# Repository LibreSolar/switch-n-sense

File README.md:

# Switch-N-Sense
High-side NMOS power switch and current sense resistor for battery applications

This device is the power part of the new generation Libre Solar 24V-48V BMS, but can also be used for lead-acid battery protection switches.

The connector to the BMS (IDC connector) is placed at the same height as in the BMS PCB. So mount this PCB right next to the BMS PCB (right side).

## Design considerations

The MOSFETs and the sense resistors are mounted at the back side of the PCB and should be attached to a large heat sink via thermal interface materials (e.g. thermal pad).

[Würth Power Elements WP-BUCF (order code 7461059)](https://powerelement.we-online.de/p/s/1406/93172-PowerOne-Bush-vertical-through-hole.html) are used for wire to board connection.

## Current target

Current rating can be adjusted depending on chosen MOSFETs and sense resistors.

- Maximum number of MOSFETs: 2 in parallel
- Maximum number of sense resitors (2512): 4

Targets for fully populated PCB (total heat dissipation approx. 20 W in MOSFETs, connectors and sense resistor at full current):

| MOSFET (2x) | Voltage | Maximum Current | Remark                                       |
|-------------|---------|-----------------|----------------------------------------------|
| FDMT80080DC | 48V     | 80 A            |                                              |
| FDMT80060DC | 12V/24V | 100 A           |                                              |
| CSD18540Q5B | 12V/24V | 60 A            | cheap alternative, but needs other footprint |

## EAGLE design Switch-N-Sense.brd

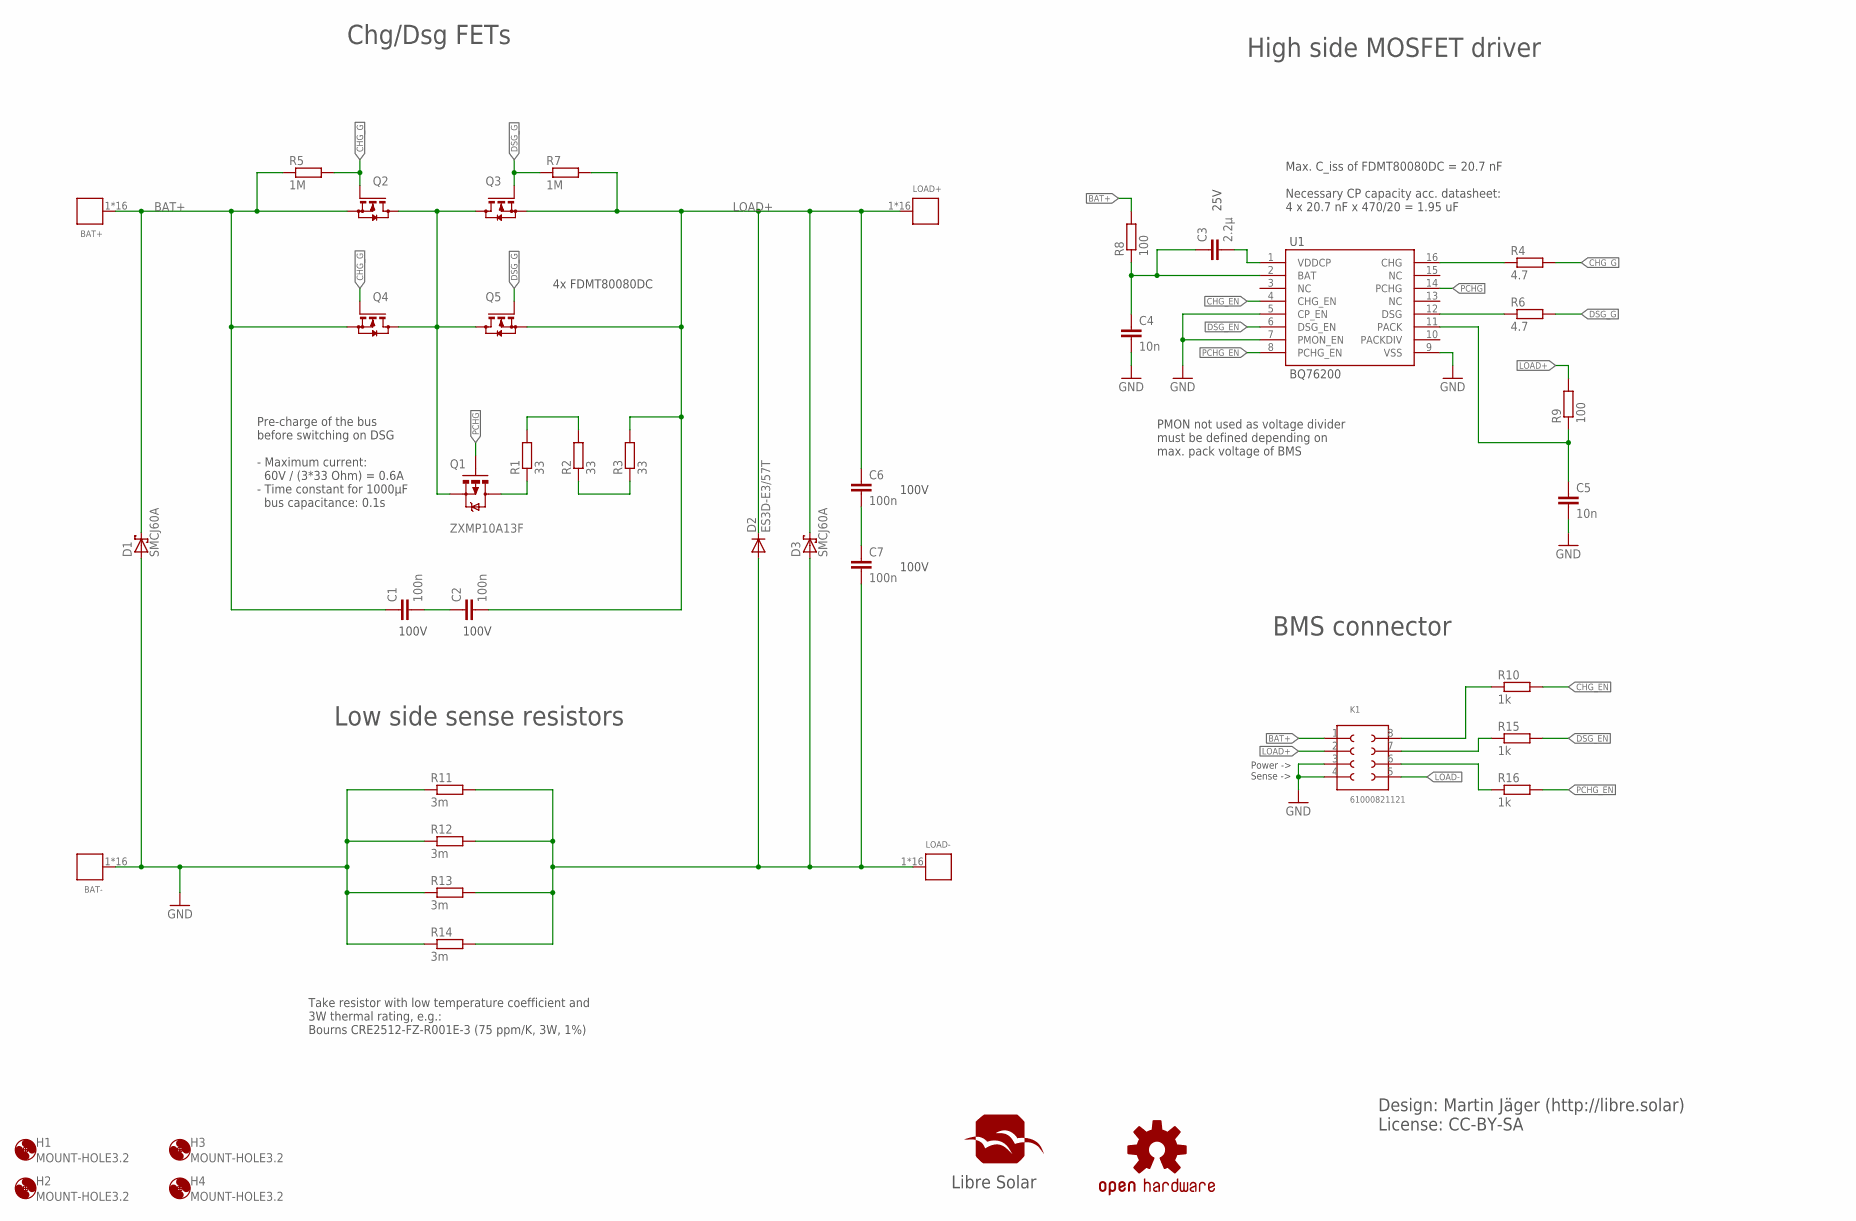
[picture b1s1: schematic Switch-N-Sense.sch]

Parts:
BAT+: WP-BUCF_G; 16PINS_CIR
BAT-: WP-BUCF_G; 16PINS_CIR
C1, C2, C6, C7: 100n; C0603; MPN 0603B104K500CT
C3: 2.2µ; C0805; MPN 0603B104K500CT
C4, C5: 10n; C0603; MPN GRM188R71H103KA01D.
D1, D3: SMCJ60A; SMC; MPN SMCJ75A
D2: ES3D-E3/57T; SMC; MPN ES3D-E3/57T.
H1, H2, H3, H4: MOUNT-HOLE3.2; 3,2
K1: 61000821121
LOAD+: WP-BUCF_G; 16PINS_CIR
LOAD-: WP-BUCF_G; 16PINS_CIR
N1: OSHW-LOGOM; OSHW-LOGO-M
Q1: ZXMP10A13F; SOT23-3; MPN ZXMP10A13FTA
Q2, Q3, Q4, Q5: FDMT80080DC
R1, R2, R3: 33; R2010; MPN ASC2010-33RFT4
R4, R6: 4.7; R0603; MPN ERJU06F1004V
R5, R7: 1M; R0603; MPN ERJU06F1004V
R8, R9: 100; R0603; MPN MCMR06X1001FTL
R10, R15, R16: 1k; R0603; MPN ERJU06F1004V
R11, R12, R13, R14: 3m; R2512
U1: BQ76200; TSSOP16
U$1: LIBRESOLAR_LOGO

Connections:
BAT+: BAT+.1, BAT+.2, BAT+.3, BAT+.4, BAT+.5, BAT+.6, BAT+.7, BAT+.8, BAT+.9, BAT+.10, BAT+.11, BAT+.12, BAT+.13, BAT+.14, BAT+.15, BAT+.16, C1.1, D1.C, K1.1, Q2.S, Q4.S, R5.1, R8.2
CHG: R4.1, U1.16 (CHG)
CHGDSG: Q1.2 (S), Q2.D, Q3.D, Q4.D, Q5.D
CHG_EN: R10.2, U1.4 (CHG_EN)
CHG_G: Q2.G, Q4.G, R4.2, R5.2
DSG: R6.1, U1.12 (DSG)
DSG_EN: R15.2, U1.6 (DSG_EN)
DSG_G: Q3.G, Q5.G, R6.2, R7.1
GND: BAT-.1, BAT-.2, BAT-.3, BAT-.4, BAT-.5, BAT-.6, BAT-.7, BAT-.8, BAT-.9, BAT-.10, BAT-.11, BAT-.12, BAT-.13, BAT-.14, BAT-.15, BAT-.16, C4.2, C5.2, D1.A, K1.3, K1.4, R11.1, R12.1, R13.1, R14.1, U1.5 (CP_EN), U1.7 (PMON_EN), U1.9 (VSS)
LOAD+: C2.2, C6.1, D2.C, D3.C, K1.2, LOAD+.1, LOAD+.2, LOAD+.3, LOAD+.4, LOAD+.5, LOAD+.6, LOAD+.7, LOAD+.8, LOAD+.9, LOAD+.10, LOAD+.11, LOAD+.12, LOAD+.13, LOAD+.14, LOAD+.15, LOAD+.16, Q3.S, Q5.S, R3.2, R7.2, R9.2
LOAD-: C7.2, D2.A, D3.A, K1.5, LOAD-.1, LOAD-.2, LOAD-.3, LOAD-.4, LOAD-.5, LOAD-.6, LOAD-.7, LOAD-.8, LOAD-.9, LOAD-.10, LOAD-.11, LOAD-.12, LOAD-.13, LOAD-.14, LOAD-.15, LOAD-.16, R11.2, R12.2, R13.2, R14.2
unnamed: C6.2, C7.1
unnamed: R1.2, R2.2
unnamed: R2.1, R3.1
unnamed: K1.7, R15.1
unnamed: K1.6, R16.1
unnamed: K1.8, R10.1
unnamed: C3.2, U1.1 (VDDCP)
unnamed: C3.1, C4.1, R8.1, U1.2 (BAT)
unnamed: C5.1, R9.1, U1.11 (PACK)
unnamed: C1.2, C2.1
unnamed: Q1.3 (D), R1.1
PCHG: Q1.1 (G), U1.14 (PCHG)
PCHG_EN: R16.2, U1.8 (PCHG_EN)

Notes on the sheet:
Pre-charge of the bus before switching on DSG - Maximum current: 60V / (3*33 Ohm) = 0.6A - Time constant for 1000µF bus capacitance: 0.1s
Chg/Dsg FETs
High side MOSFET driver
Design: Martin Jäger (http://libre.solar) License: CC-BY-SA
Max. C_iss of FDMT80080DC = 20.7 nF Necessary CP capacity acc. datasheet: 4 x 20.7 nF x 470/20 = 1.95 uF
4x FDMT80080DC
Take resistor with low temperature coefficient and 3W thermal rating, e.g.: Bourns CRE2512-FZ-R001E-3 (75 ppm/K, 3W, 1%)
Low side sense resistors
BMS connector
Power -> Sense ->
PMON not used as voltage divider must be defined depending on max. pack voltage of BMS
100V
25V

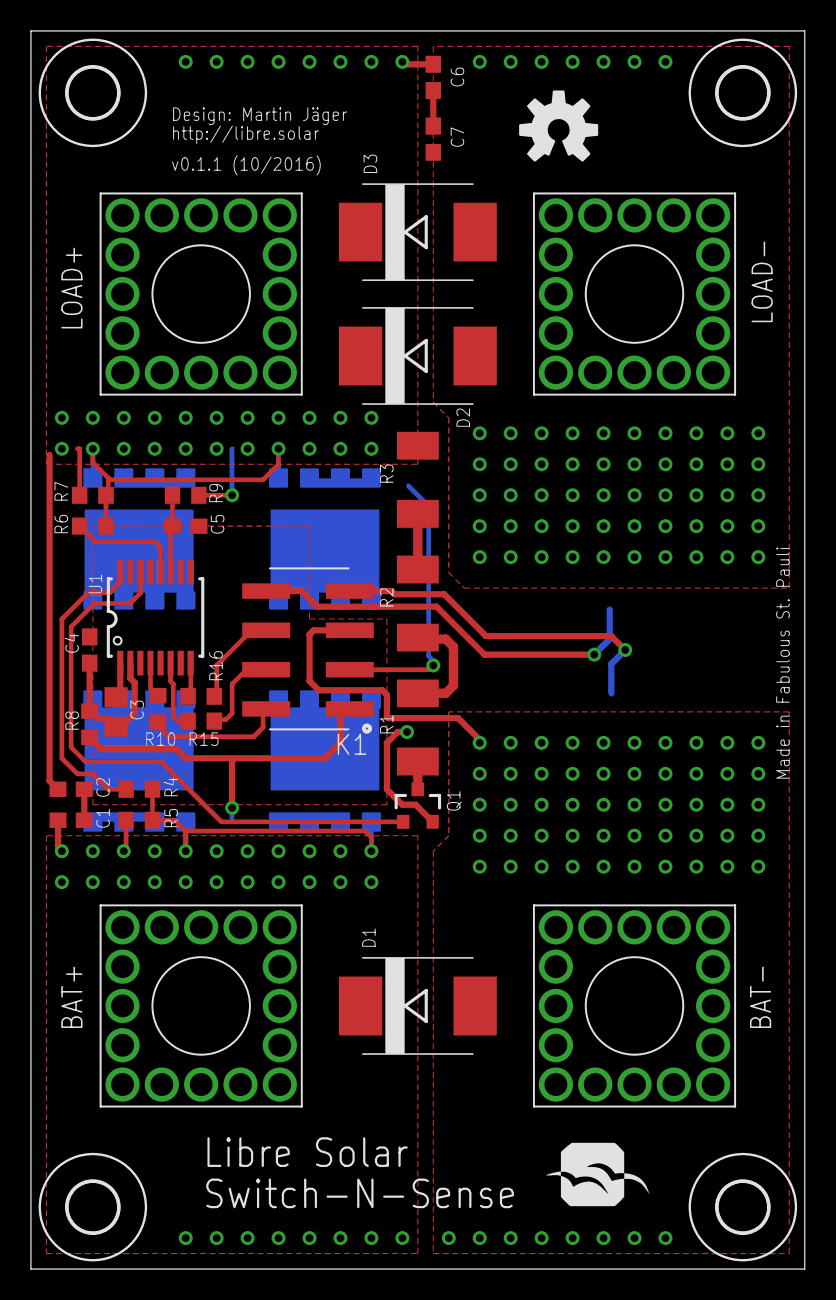
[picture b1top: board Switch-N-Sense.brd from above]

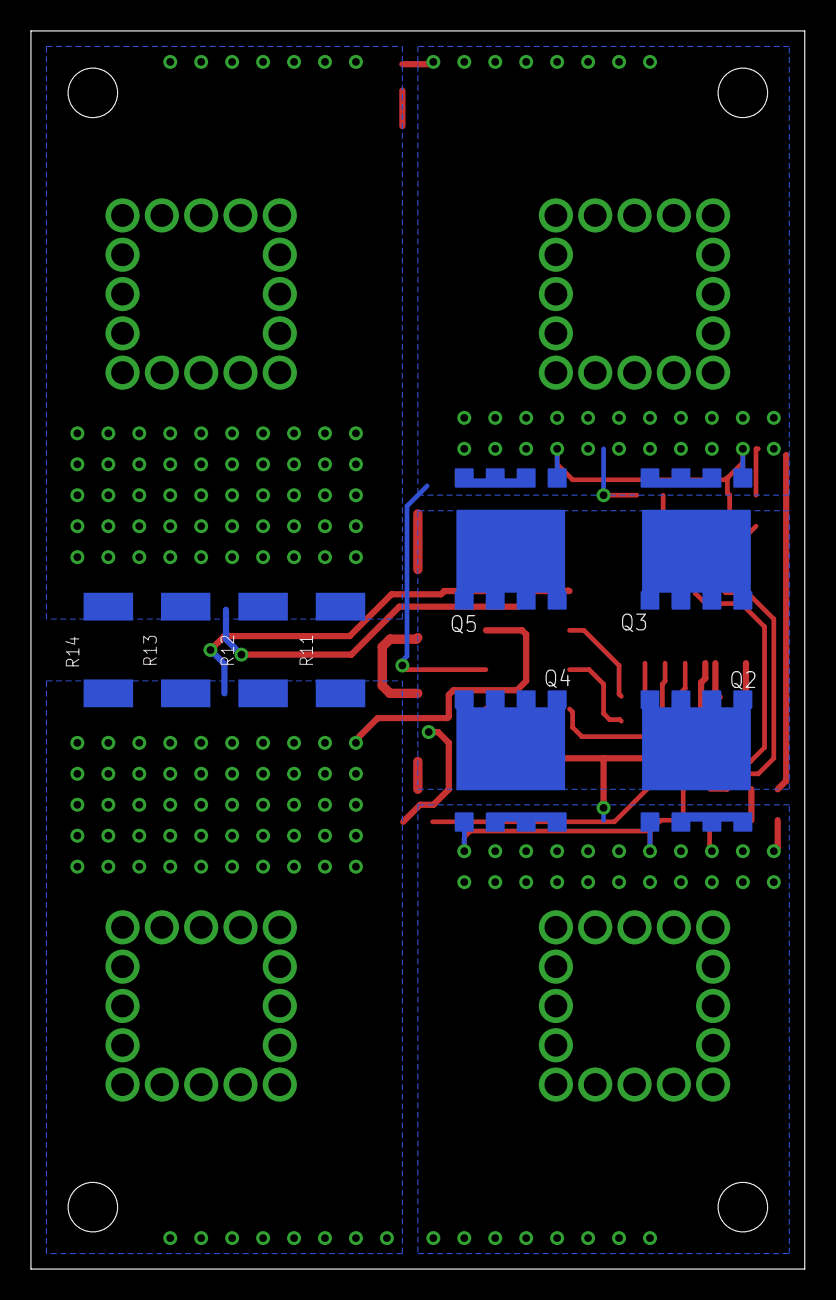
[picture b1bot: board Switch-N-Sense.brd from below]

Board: 2 copper layers, 50.0 x 80.0 mm, 43 parts (8 on the bottom side), 24 nets.

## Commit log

2016-08-15 Initial commit of schematic and board
2016-10-03 Update to mate with new LibreSolar BMS48V
2016-10-12 Updated board and schematic to fix issue #1

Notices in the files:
parts and their libraries:
SparkFun-DiscreteSemi: Licensing: Creative Commons ShareAlike 4.0 International - https://creativecommons.org/licenses/by-sa/4.0
Wuerth_Elektronik_Power_Elements_rev15c: Copyright: Würth Elektronik
